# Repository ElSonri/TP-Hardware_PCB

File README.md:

# TP-Hardware_PCB
Diseño de PCB para Trabajo Profesional de Ing. Electronica

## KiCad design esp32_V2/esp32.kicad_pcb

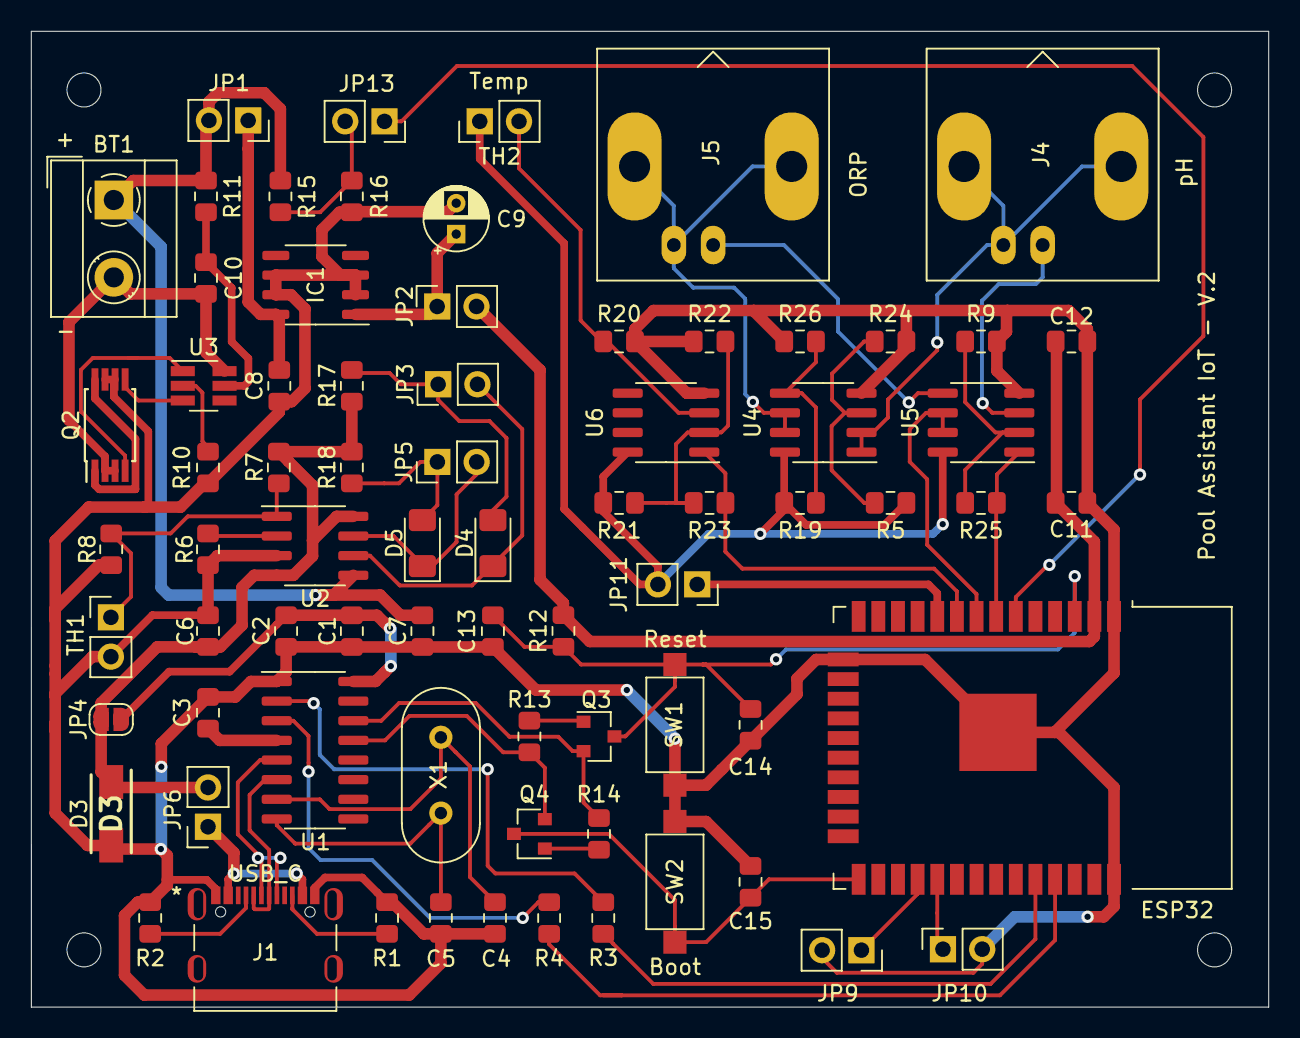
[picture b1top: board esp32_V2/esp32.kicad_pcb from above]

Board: 2 copper layers, 80.0 x 63.1 mm, 78 parts (0 on the bottom side), 55 nets.

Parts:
BT1: LCR26650; TerminalBlock_MetzConnect_Type055_RT01502HDWU_1x02_P5.00mm_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
C1, C11: 10u; C_0805_2012Metric_Pad1.15x1.40mm_HandSolder
C2, C3, C12: 0.1u; C_0805_2012Metric_Pad1.15x1.40mm_HandSolder
C4, C5: 22p; C_0805_2012Metric_Pad1.15x1.40mm_HandSolder
C6, C7: 10uF; C_0805_2012Metric_Pad1.15x1.40mm_HandSolder
C8: 1uF; C_0805_2012Metric_Pad1.15x1.40mm_HandSolder
C9: 10uF; CP_Radial_D4.0mm_P2.00mm
C10, C14, C15: 0.1uF; C_0805_2012Metric_Pad1.15x1.40mm_HandSolder
C13: 1u; C_0805_2012Metric_Pad1.15x1.40mm_HandSolder
D3: SMAJ5.0A; DIOM5026X229N
D4: READY; LED_1206_3216Metric_Pad1.42x1.75mm_HandSolder
D5: CHRG; LED_1206_3216Metric_Pad1.42x1.75mm_HandSolder
ESP32: ESP32-WROOM-32
Hole2, Hole2#2, Hole2#3, Hole2#4: MountingHole_2.2mm_M2_ISO7380
IC1: KF33BD-TR; SO-8_3.9x4.9mm_P1.27mm
J1: USB_C; 12402012E212A
J4: pH; BNC_Amphenol_B6252HB-NPP3G-50_Horizontal
J5: ORP; BNC_Amphenol_B6252HB-NPP3G-50_Horizontal
JP1, JP2, JP6, JP9, JP10, JP11, JP13: Jumper_NO; PinSocket_1x02_P2.54mm_Vertical
JP3: READY; PinHeader_1x02_P2.54mm_Vertical
JP4: SolderJumper_NO; SolderJumper-2_P1.3mm_Open_RoundedPad1.0x1.5mm
JP5: CHRG; PinHeader_1x02_P2.54mm_Vertical
Q2: 8205A; TSSOP-8_4.4x3mm_P0.65mm
Q3, Q4: BC817; SOT-23
R1, R2: 5.1k; R_0805_2012Metric_Pad1.15x1.40mm_HandSolder
R3, R4, R11: 100; R_0805_2012Metric_Pad1.15x1.40mm_HandSolder
R5, R19: 50K; R_0805_2012Metric_Pad1.15x1.40mm_HandSolder
R6: 1.2k; R_0805_2012Metric_Pad1.15x1.40mm_HandSolder
R7: RT1; R_0805_2012Metric_Pad1.15x1.40mm_HandSolder
R8: RT2; R_0805_2012Metric_Pad1.15x1.40mm_HandSolder
R9, R12, R13, R14, R25: 10k; R_0805_2012Metric_Pad1.15x1.40mm_HandSolder
R10: 1k; R_0805_2012Metric_Pad1.15x1.40mm_HandSolder
R15: 39k; R_0805_2012Metric_Pad1.15x1.40mm_HandSolder
R16: 50k; R_0805_2012Metric_Pad1.15x1.40mm_HandSolder
R17, R18: 220; R_0805_2012Metric_Pad1.15x1.40mm_HandSolder
R20: 4k7; R_0805_2012Metric_Pad1.15x1.40mm_HandSolder
R21: 180k; R_0805_2012Metric_Pad1.15x1.40mm_HandSolder
R22: 150k; R_0805_2012Metric_Pad1.15x1.40mm_HandSolder
R23: 27k; R_0805_2012Metric_Pad1.15x1.40mm_HandSolder
R24, R26: R_Small; R_0805_2012Metric_Pad1.15x1.40mm_HandSolder
SW1: Reset; SW_SPST_CK_RS282G05A3
SW2: Boot; SW_SPST_CK_RS282G05A3
TH1: NTC; PinHeader_1x02_P2.54mm_Vertical
TH2: NTC2; PinHeader_1x02_P2.54mm_Vertical
U1: CH340G; SOIC-16_3.9x9.9mm_P1.27mm
U2: TC4056; SOIC-8_3.9x4.9mm_P1.27mm
U3: DW01A; SOT-23-6_Handsoldering
U4, U6: LM358; SOIC-8_3.9x4.9mm_P1.27mm
U5: TLC272; SOIC-8_3.9x4.9mm_P1.27mm
X1: 12 MHz; Crystal_HC18-U_Vertical

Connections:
28: ESP32.28, JP9.1
29: ESP32.29, JP10.1
+3V3: C11.1, C12.2, ESP32.2, JP2.2, R12.1
Bat: ESP32.6, JP13.1
Batt+: BT1.1, C7.1, JP1.2, R11.1, R15.1, U2.5
Batt-: BT1.2, C10.2, Q2.2, Q2.3, U3.6
Boot: C15.1, ESP32.25, Q4.3, SW2.1
Cl: ESP32.8, U5.6, U5.7
D+: J1.A6, J1.B6, U1.5
D-: J1.A7, J1.B7, U1.6
DTR: Q4.2, R13.2, U1.13
EN: C13.1, C14.1, ESP32.3, Q3.3, R12.2, SW1.1
GND: C1.2, C2.2, C3.2, C4.2, C5.2, C6.2, C7.2, C8.2, C9.2, C11.2, C12.1, C13.2, C14.2, C15.2, D3.2, ESP32.1, ESP32.15, ESP32.38, IC1.2, IC1.3, IC1.6, IC1.7, J1.A1-B12, J1.B1-A12, JP9.2, JP10.2, Q2.6, Q2.7, R1.2, R2.2, R6.2, R8.2, R9.1, R10.2, R16.2, R20.1, R22.2, R24.2, R26.2, SW1.2, SW2.2, TH1.2, U1.1, U2.3, U4.4, U5.4, U6.4
unnamed: C1.1, C2.1, JP4.1, U1.16
unnamed: C3.1, U1.4
unnamed: C4.1, U1.7, X1.1
unnamed: C5.1, U1.8, X1.2
unnamed: C8.1, IC1.8, JP1.1
unnamed: C9.1, IC1.1, JP2.1
unnamed: C10.1, R11.2, U3.5
unnamed: D4.1, JP3.2, U2.6
unnamed: D4.2, JP3.1, R17.2
unnamed: D5.1, JP5.2, U2.7
unnamed: D5.2, JP5.1, R18.2
unnamed: ESP32.10, JP11.1
unnamed: J1.A4-B9, J1.B4-A9, JP6.1
unnamed: J1.A5, R2.1
unnamed: J1.B5, R1.1
unnamed: JP13.2, R15.2, R16.1
unnamed: Q2.1, Q2.8
unnamed: Q2.4, U3.1
unnamed: Q2.5, U3.3
unnamed: Q3.1, R13.1
unnamed: Q4.1, R14.1
unnamed: R3.2, U1.2
unnamed: R4.2, U1.3
unnamed: R6.1, U2.2
unnamed: R7.2, R8.1, TH1.1, U2.1
unnamed: R10.1, U3.2
unnamed: R19.1, R26.1, U4.5
unnamed: R20.2, TH2.2, U6.3
unnamed: R21.2, R22.1, R23.2, U6.2
unnamed: R5.1, R24.1, U4.3
unnamed: R9.2, R25.1, U5.2
ORP+: J5.1, U5.5
ORP-: J5.2, U4.6, U4.7
RTS: Q3.2, R14.2, U1.14
Rx: ESP32.34, R3.1
Temp: ESP32.9, R23.1, U6.1
Tx: ESP32.35, R4.1
VBUS: C6.1, D3.1, JP4.2, JP6.2, R7.1, R17.1, R18.1, U2.4, U2.8
Vcc: JP11.2, R5.2, R19.2, R21.1, TH2.1, U4.8, U5.8, U6.8
pH: ESP32.7, R25.2, U5.1
pH+: J4.1, U5.3
pH-: J4.2, U4.1, U4.2

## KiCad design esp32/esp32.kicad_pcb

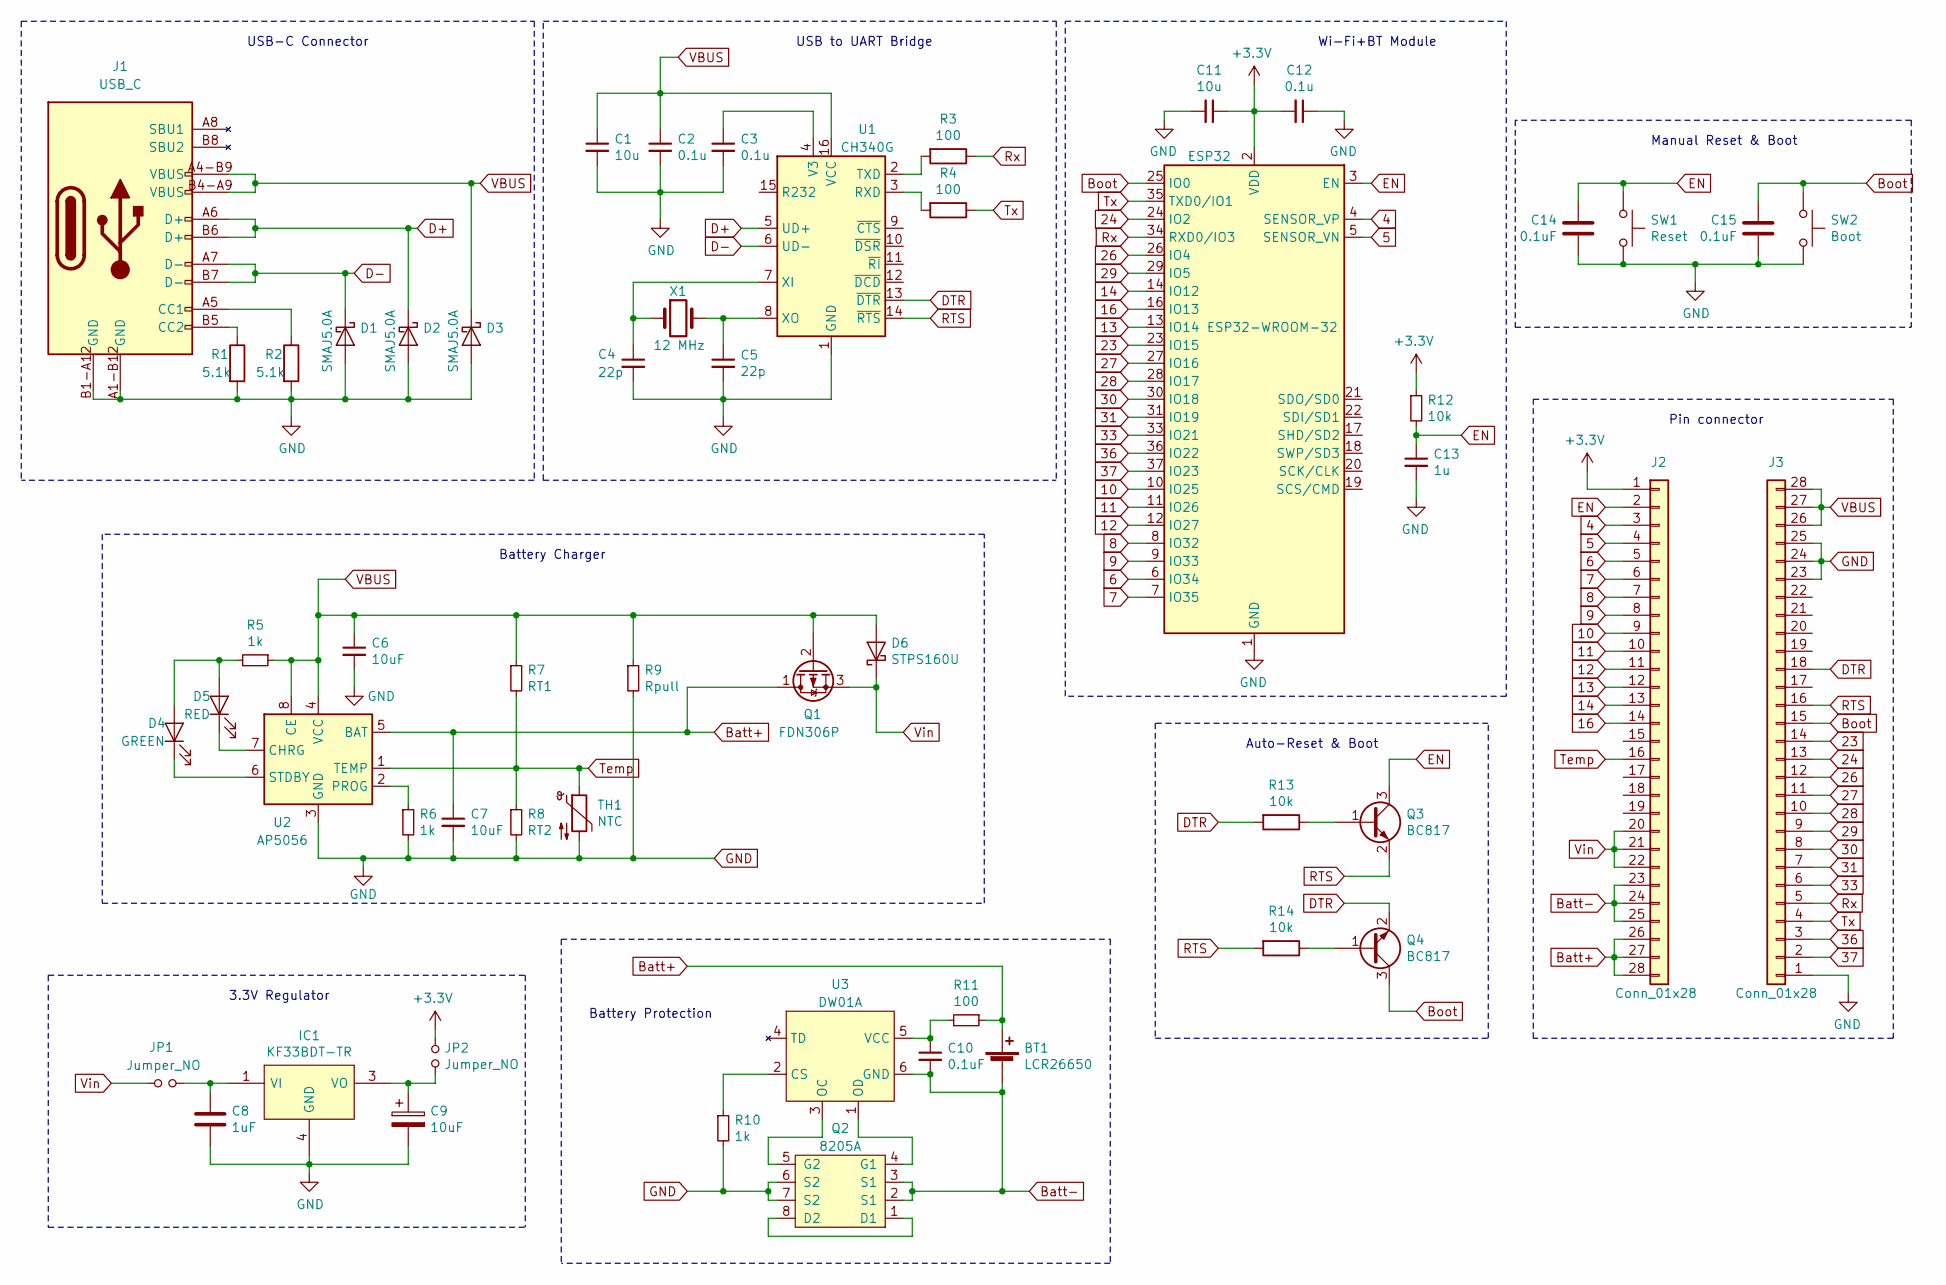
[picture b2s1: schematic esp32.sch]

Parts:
BT1: LCR26650; TerminalBlock_MetzConnect_Type055_RT01502HDWU_1x02_P5.00mm_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
C1, C11: 10u; C_0805_2012Metric_Pad1.15x1.40mm_HandSolder
C2, C3, C12: 0.1u; C_0805_2012Metric_Pad1.15x1.40mm_HandSolder
C4, C5: 22p; C_0805_2012Metric_Pad1.15x1.40mm_HandSolder
C6, C7: 10uF; C_0805_2012Metric_Pad1.15x1.40mm_HandSolder
C8: 1uF; C_0805_2012Metric_Pad1.15x1.40mm_HandSolder
C9: 10uF; CP_Radial_D4.0mm_P2.00mm
C10, C14, C15: 0.1uF; C_0805_2012Metric_Pad1.15x1.40mm_HandSolder
C13: 1u; C_0805_2012Metric_Pad1.15x1.40mm_HandSolder
D1, D2, D3: SMAJ5.0A; DIOM5026X229N
D4: GREEN; LED_1206_3216Metric_Pad1.42x1.75mm_HandSolder
D5: RED; LED_1206_3216Metric_Pad1.42x1.75mm_HandSolder
D6: STPS160U; D_SMB_Handsoldering
ESP32: ESP32-WROOM-32
IC1: KF33BDT-TR; TO228P972X240-3N; Manufacturer_Part_Number KF33BDT-TR; Mouser Part Number 511-KF33BDT-TR
J1: USB_C; 12402012E212A
J2, J3: Conn_01x28; PinHeader_1x28_P2.54mm_Vertical
JP1, JP2: Jumper_NO; PinSocket_1x02_P2.54mm_Vertical
Q1: FDN306P; SuperSOT-3
Q2: 8205A; TSSOP-8_4.4x3mm_P0.65mm
Q3, Q4: BC817; SOT-23
R1, R2: 5.1k; R_0805_2012Metric_Pad1.15x1.40mm_HandSolder
R3, R4, R11: 100; R_0805_2012Metric_Pad1.15x1.40mm_HandSolder
R5, R6, R10: 1k; R_0805_2012Metric_Pad1.15x1.40mm_HandSolder
R7: RT1; R_0805_2012Metric_Pad1.15x1.40mm_HandSolder
R8: RT2; R_0805_2012Metric_Pad1.15x1.40mm_HandSolder
R9: Rpull; R_0805_2012Metric_Pad1.15x1.40mm_HandSolder
R12, R13, R14: 10k; R_0805_2012Metric_Pad1.15x1.40mm_HandSolder
SW1: Reset; SW_SPST_B3U-1000P
SW2: Boot; SW_SPST_B3U-1000P
TH1: NTC; R_1206_3216Metric_Pad1.42x1.75mm_HandSolder
U1: CH340G; SOIC-16_3.9x9.9mm_P1.27mm
U2: AP5056; SOIC-8_3.9x4.9mm_P1.27mm
U3: DW01A; SOT-23-6_Handsoldering
X1: 12 MHz; Crystal_HC18-U_Vertical

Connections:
4: ESP32.4 (SENSOR_VP), J2.3
5: ESP32.5 (SENSOR_VN), J2.4
6: ESP32.6 (IO34), J2.5
7: ESP32.7 (IO35), J2.6
8: ESP32.8 (IO32), J2.7
9: ESP32.9 (IO33), J2.8
10: ESP32.10 (IO25), J2.9
11: ESP32.11 (IO26), J2.10
12: ESP32.12 (IO27), J2.11
13: ESP32.13 (IO14), J2.12
14: ESP32.14 (IO12), J2.13
16: ESP32.16 (IO13), J2.14
23: ESP32.23 (IO15), J3.14
24: ESP32.24 (IO2), J3.13
26: ESP32.26 (IO4), J3.12
27: ESP32.27 (IO16), J3.11
28: ESP32.28 (IO17), J3.10
29: ESP32.29 (IO5), J3.9
30: ESP32.30 (IO18), J3.8
31: ESP32.31 (IO19), J3.7
33: ESP32.33 (IO21), J3.6
36: ESP32.36 (IO22), J3.3
37: ESP32.37 (IO23), J3.2
+3V3: C11.1, C12.2, ESP32.2 (VDD), J2.1, JP2.2, R12.1
Batt+: BT1.1 (+), C7.1, J2.26, J2.27, J2.28, Q1.1 (D), R11.1, U2.5 (BAT)
Batt-: BT1.2 (-), C10.2, J2.23, J2.24, J2.25, Q2.2 (S1), Q2.3 (S1), U3.6 (GND)
Boot: C15.1, ESP32.25 (IO0), J3.15, Q4.3 (C), SW2.1
D+: D2.1 (K), J1.A6 (D+), J1.B6 (D+), U1.5 (UD+)
D-: D1.1 (K), J1.A7 (D-), J1.B7 (D-), U1.6 (UD-)
DTR: J3.18, Q4.2 (E), R13.2, U1.13 (~DTR)
EN: C13.1, C14.1, ESP32.3 (EN), J2.2, Q3.3 (C), R12.2, SW1.1
GND: C1.2, C2.2, C3.2, C4.2, C5.2, C6.2, C7.2, C8.2, C9.2, C11.2, C12.1, C13.2, C14.2, C15.2, D1.2 (A), D2.2 (A), D3.2 (A), ESP32.1 (GND), ESP32.15 (GND), ESP32.38 (GND), IC1.4 (GND), J1.A1-B12 (GND), J1.B1-A12 (GND), J3.1, J3.23, J3.24, J3.25, Q2.6 (S2), Q2.7 (S2), R1.2, R2.2, R6.2, R8.2, R9.2, R10.2, SW1.2, SW2.2, TH1.2, U1.1 (GND), U2.3 (GND)
unnamed: C3.1, U1.4 (V3)
unnamed: C4.1, U1.7 (XI), X1.1
unnamed: C5.1, U1.8 (XO), X1.2
unnamed: C8.1, IC1.1 (VI), JP1.2
unnamed: C9.1, IC1.3 (VO), JP2.1
unnamed: C10.1, R11.2, U3.5 (VCC)
unnamed: D4.1 (K), U2.6 (STDBY)
unnamed: D4.2 (A), D5.2 (A), R5.2
unnamed: D5.1 (K), U2.7 (CHRG)
unnamed: J1.A5 (CC1), R2.1
unnamed: J1.B5 (CC2), R1.1
unnamed: Q2.1 (D1), Q2.8 (D2)
unnamed: Q2.4 (G1), U3.1 (OD)
unnamed: Q2.5 (G2), U3.3 (OC)
unnamed: Q3.1 (B), R13.1
unnamed: Q4.1 (B), R14.1
unnamed: R3.2, U1.2 (TXD)
unnamed: R4.2, U1.3 (RXD)
unnamed: R6.1, U2.2 (PROG)
unnamed: R10.1, U3.2 (CS)
RTS: J3.16, Q3.2 (E), R14.2, U1.14 (~RTS)
Rx: ESP32.34 (RXD0/IO3), J3.5, R3.1
Temp: J2.16, R7.2, R8.1, TH1.1, U2.1 (TEMP)
Tx: ESP32.35 (TXD0/IO1), J3.4, R4.1
VBUS: C1.1, C2.1, C6.1, D3.1 (K), D6.2 (A), J1.A4-B9 (VBUS), J1.B4-A9 (VBUS), J3.26, J3.27, J3.28, Q1.2 (G), R5.1, R7.1, R9.1, U1.16 (VCC), U2.4 (VCC), U2.8 (CE)
Vin: D6.1 (K), J2.20, J2.21, J2.22, JP1.1, Q1.3 (S)

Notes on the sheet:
Battery Protection
Auto-Reset & Boot
Battery Charger
Pin connector
Manual Reset & Boot
Wi-Fi+BT Module
USB-C Connector
3.3V Regulator
USB to UART Bridge

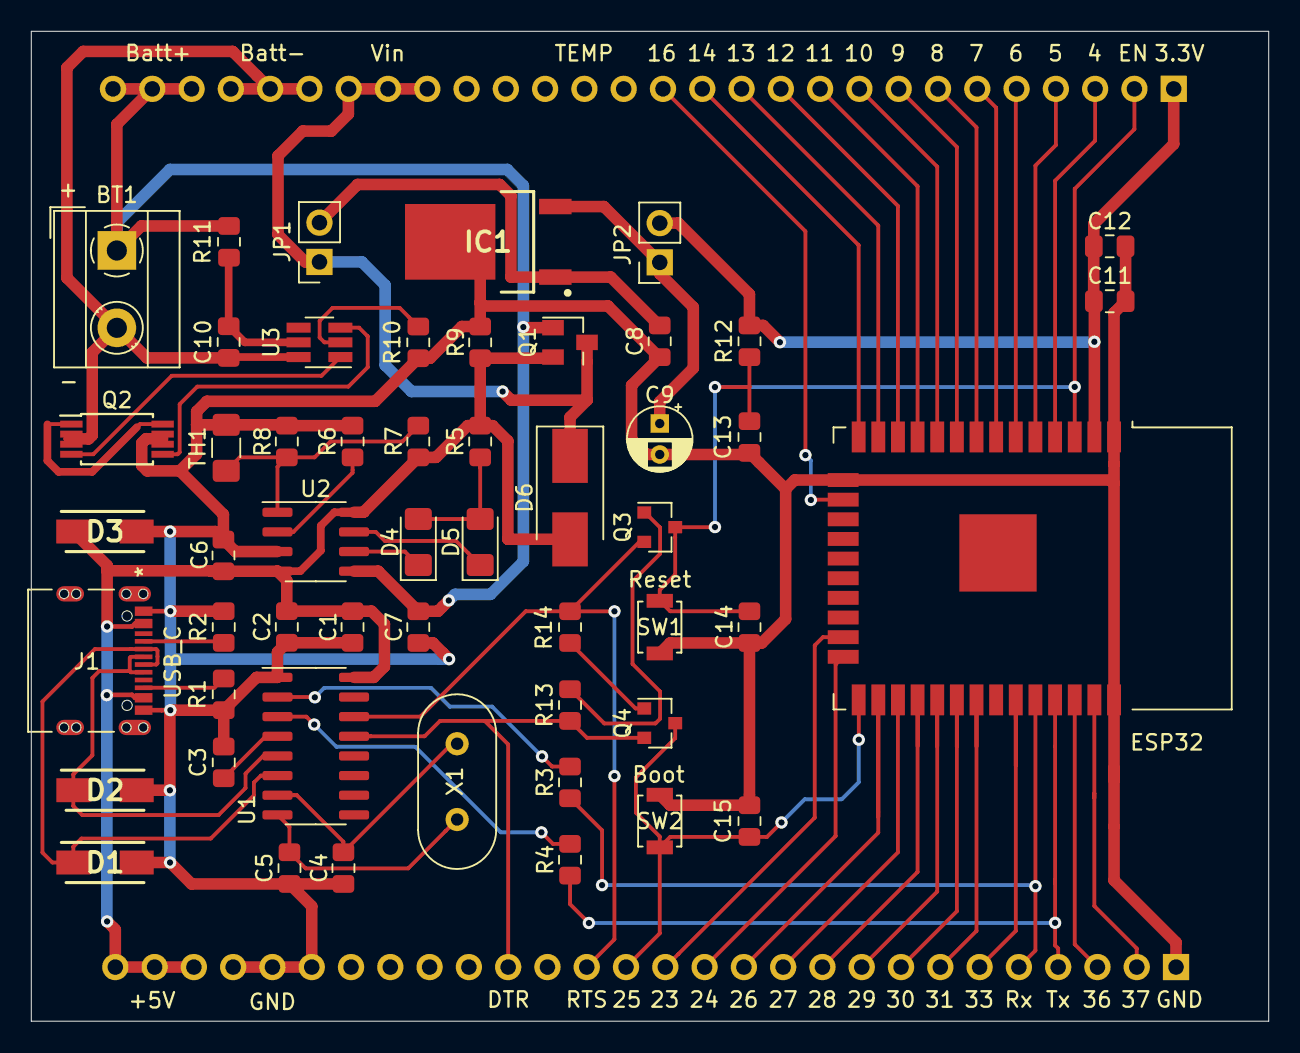
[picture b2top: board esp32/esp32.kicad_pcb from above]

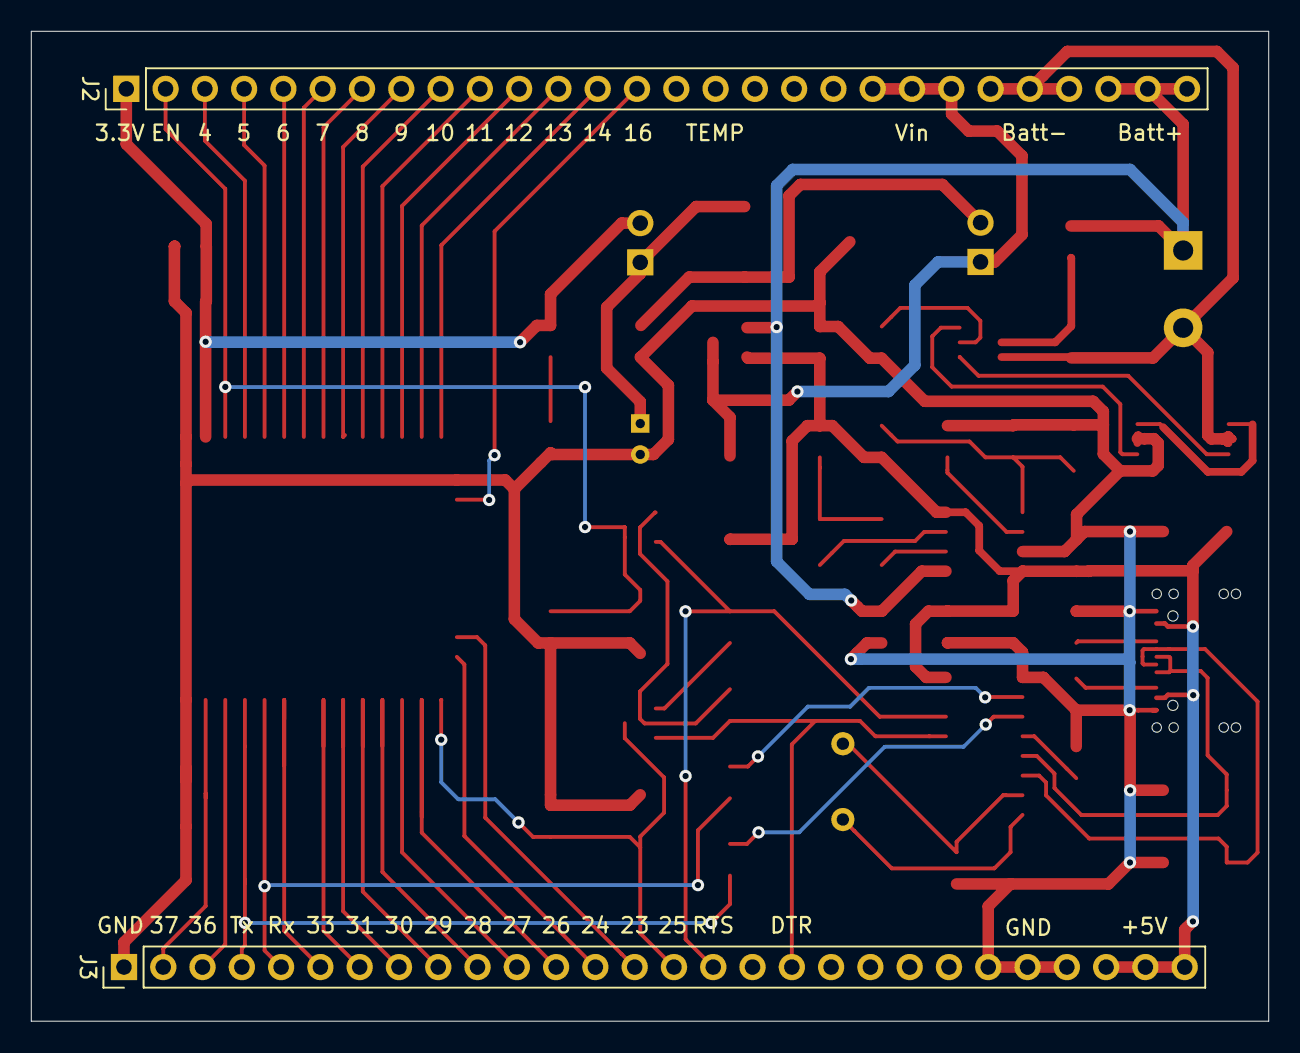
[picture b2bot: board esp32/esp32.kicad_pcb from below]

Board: 2 copper layers, 80.0 x 64.0 mm, 54 parts (2 on the bottom side), 58 nets.

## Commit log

2022-06-07 Esquematico con ESP32, cargador usb-c y conversor usb a uart. PCB sin routear
2022-06-07 Borrar proyecto de KiCad duplicado
2022-06-18 Add PCB routing
2022-06-18 1) Power tracks to 30 milis - 2) Add more pins for symmetry
2022-06-28 Cambio de componentes: 1) USB-to-UART (CH340G por CP2102) 2) Dual Mosfet (8205A por FDS9926A)
2022-07-04 1) Medicion de bateria - 2) Agujeros para tornillos - 3) Nombre de integarntes y proyecto
2022-09-08 Agregar simulaciones de sensores
2022-09-26 PCB initial V2
2022-09-26 Finished routing
2022-09-28 Made final changes. Added jumpers for Vcc, bat and buttons
2022-09-28 Add Holes, R1 and R2 to V2.1
2022-09-29 Refactor some tracks
2022-09-30 Update gerbers and drill files
2022-09-30 Remove V2 folder and rename V2.1 folder to V2
2022-11-06 1) Correct components values in measurement circuits - 2) Schematic cleanup - 3) Fix tracks in PCB - 4) Add Thermistor calculator

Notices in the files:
parts and their libraries:
Copyright 2021 Accelerated Designs. All rights reserved.
